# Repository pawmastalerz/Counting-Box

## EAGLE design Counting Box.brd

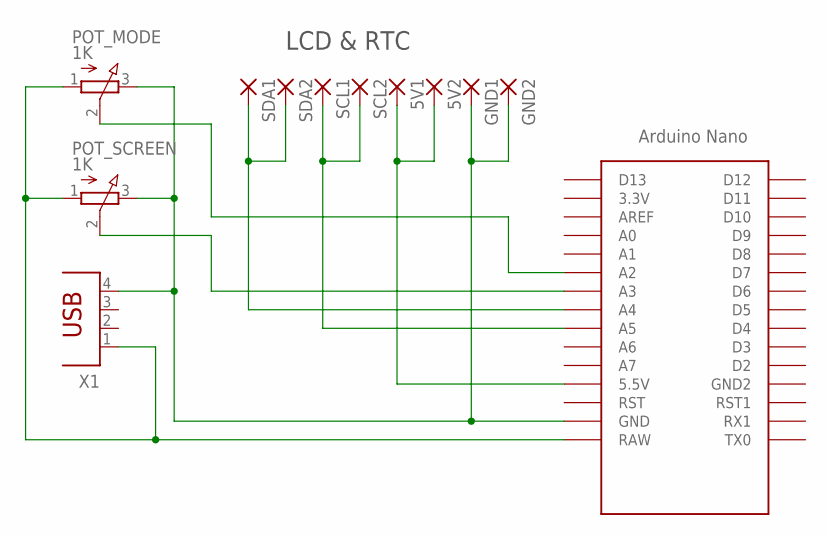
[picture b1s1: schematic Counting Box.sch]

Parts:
5V1, 5V2: SMD2; SMD1,27-2,54
GND1, GND2: SMD2; SMD1,27-2,54
POT_MODE: 1K; 3RP/1610N
POT_SCREEN: 1K; 3RP/1610N
SCL1, SCL2: SMD2; SMD1,27-2,54
SDA1, SDA2: SMD2; SMD1,27-2,54
U$1: NANO
X1: PN87520

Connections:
5V: 5V1.1, 5V2.1, U$1.5V (5.5V)
GND: GND1.1, GND2.1, POT_MODE.3 (E), POT_SCREEN.3 (E), U$1.GND, X1.4
POT_MODE: POT_MODE.2 (S), U$1.A2
POT_SCREEN: POT_SCREEN.2 (S), U$1.A3
SCL: SCL1.1, SCL2.1, U$1.A5
SDA: SDA1.1, SDA2.1, U$1.A4
VCC: POT_MODE.1 (A), POT_SCREEN.1 (A), U$1.RAW, X1.1

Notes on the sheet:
LCD & RTC

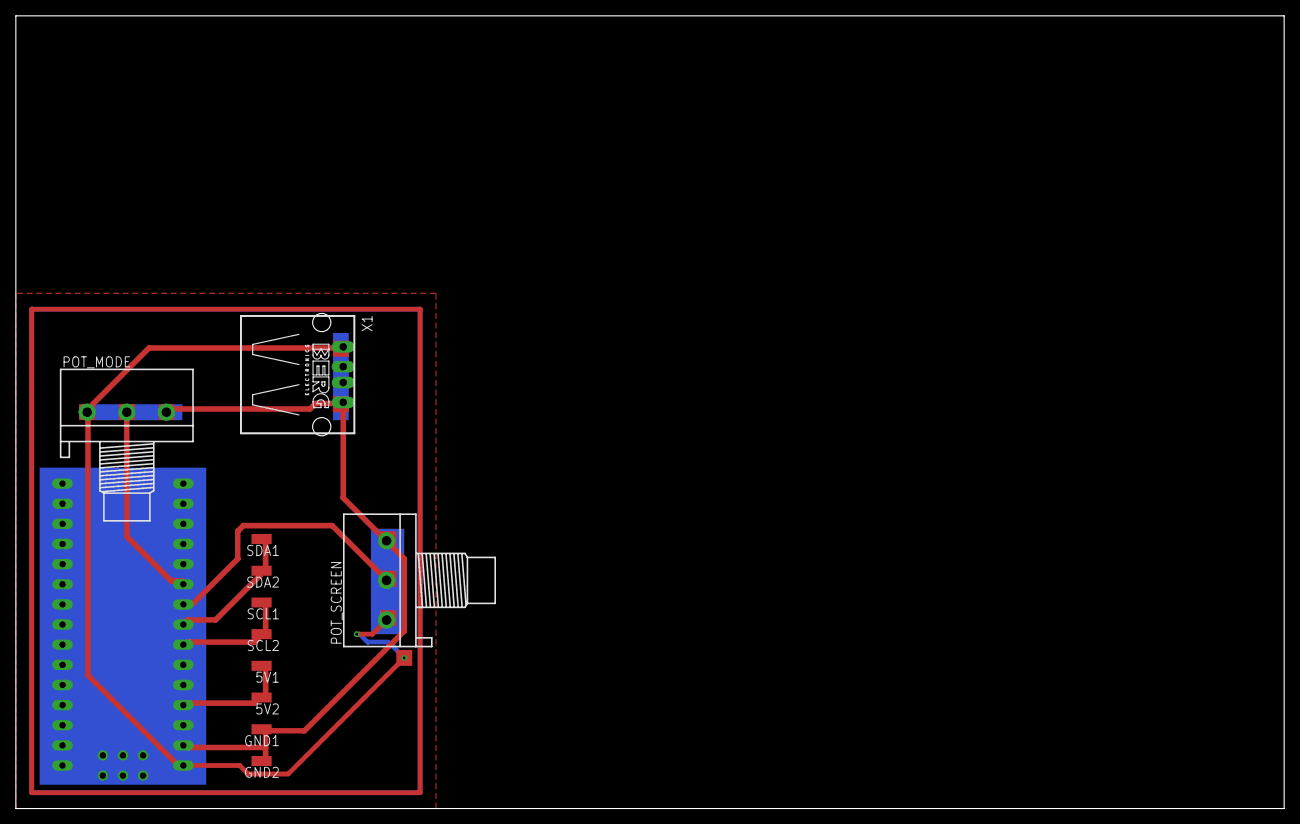
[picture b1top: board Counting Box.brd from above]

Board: 2 copper layers, 160.0 x 100.0 mm, 12 parts (1 on the bottom side), 7 nets.

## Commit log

2017-10-17 Initial commit.
2017-10-17 Get current date and print to Serial.
2017-10-17 Quick test.
2017-10-17 Minor changes.
2017-10-29 Print minutes and seconds to LCD
2017-10-29 Display secs, mins, hrs & days.
2017-10-29 Turn LCD backlight on/off on interruption.
    Things that require changes:
    1) Interruption
    2) loop() - DRY! Try switch-case.
2017-10-29 Interruption changed to analogRead.
2017-10-29 Project seems completed.
    To do:
    - Months / Years?...
2017-10-29 Eagle schematic
2017-11-02 Print setup errors to LCD.
2017-11-02 Pre -alpha version of displaying number of months.
2017-11-02 Early beta version. Project works. Months and years visible.
    1) The code could be neater and easier to interpret.
    2) Maybe the text printed to LCD could be nicely centered, lower numbers look kinda funny.
2017-11-10 Eagle board, code fixes.
2017-11-10 Minor code changes.
2017-11-12 Code description, minor changes.
2017-12-22 Added second potentiometer to schematic.
2018-04-09 DateTime to timestamp conversion.
